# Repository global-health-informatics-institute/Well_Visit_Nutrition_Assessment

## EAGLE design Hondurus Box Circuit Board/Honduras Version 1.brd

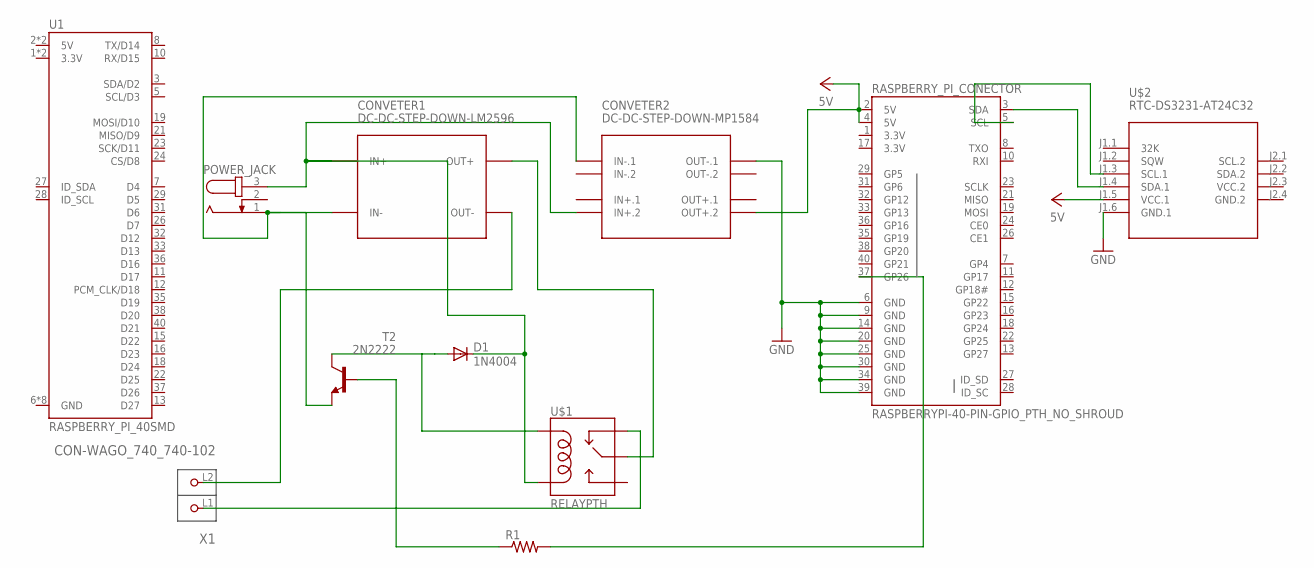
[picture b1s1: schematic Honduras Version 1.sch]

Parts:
CONVETER1: DC-DC-STEP-DOWN-LM2596
CONVETER2: DC-DC-STEP-DOWN-MP1584
D1: 1N4004; DO41-10
POWER_JACK: JACK-PLUG0; SPC4077
R1: R-US_0207/10; 0207/10
RASPBERRY_PI_CONECTOR: RASPBERRYPI-40-PIN-GPIO_PTH_NO_SHROUD; 2X20
T2: 2N2222; TO92-EBC-OVAL
U1: RASPBERRY_PI_40SMD; RASPBERRY_PI_SHIELD_HOLES
U$1: RELAYPTH; SRD-05VDC-SL-C
U$2: RTC-DS3231-AT24C32
X1: CON-WAGO_740_740-102; CON-WAGO_740_P-740-102

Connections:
3.3V: RASPBERRY_PI_CONECTOR.1 (3.3V), RASPBERRY_PI_CONECTOR.17 (3.3V)
GND: CONVETER2.OUT-.1, RASPBERRY_PI_CONECTOR.6 (GND), RASPBERRY_PI_CONECTOR.9 (GND), RASPBERRY_PI_CONECTOR.14 (GND), RASPBERRY_PI_CONECTOR.20 (GND), RASPBERRY_PI_CONECTOR.25 (GND), RASPBERRY_PI_CONECTOR.30 (GND), RASPBERRY_PI_CONECTOR.34 (GND), RASPBERRY_PI_CONECTOR.39 (GND), U$2.J1.6 (GND.1)
GND.2: U$2.J2.4 (GND.2)
unnamed: CONVETER1.IN+, CONVETER2.IN+.2, D1.C, POWER_JACK.3, U$1.COIL0
unnamed: RASPBERRY_PI_CONECTOR.3 (SDA), U$2.J1.4 (SDA.1)
unnamed: RASPBERRY_PI_CONECTOR.5 (SCL), U$2.J1.3 (SCL.1)
unnamed: CONVETER1.OUT-, X1.L2 (P2)
unnamed: CONVETER1.IN-, CONVETER2.IN-.1, POWER_JACK.1, T2.E
unnamed: R1.2, RASPBERRY_PI_CONECTOR.37 (GP26)
unnamed: D1.A, T2.C, U$1.COIL1
unnamed: R1.1, T2.B
unnamed: U$1.SWCLOSED (SWCLOSE), X1.L1 (P1)
unnamed: CONVETER1.OUT+, U$1.SWCOMMON
VCC: CONVETER2.OUT+.2, RASPBERRY_PI_CONECTOR.2 (5V), RASPBERRY_PI_CONECTOR.4 (5V), U$2.J1.5 (VCC.1)
VCC.2: U$2.J2.3 (VCC.2)

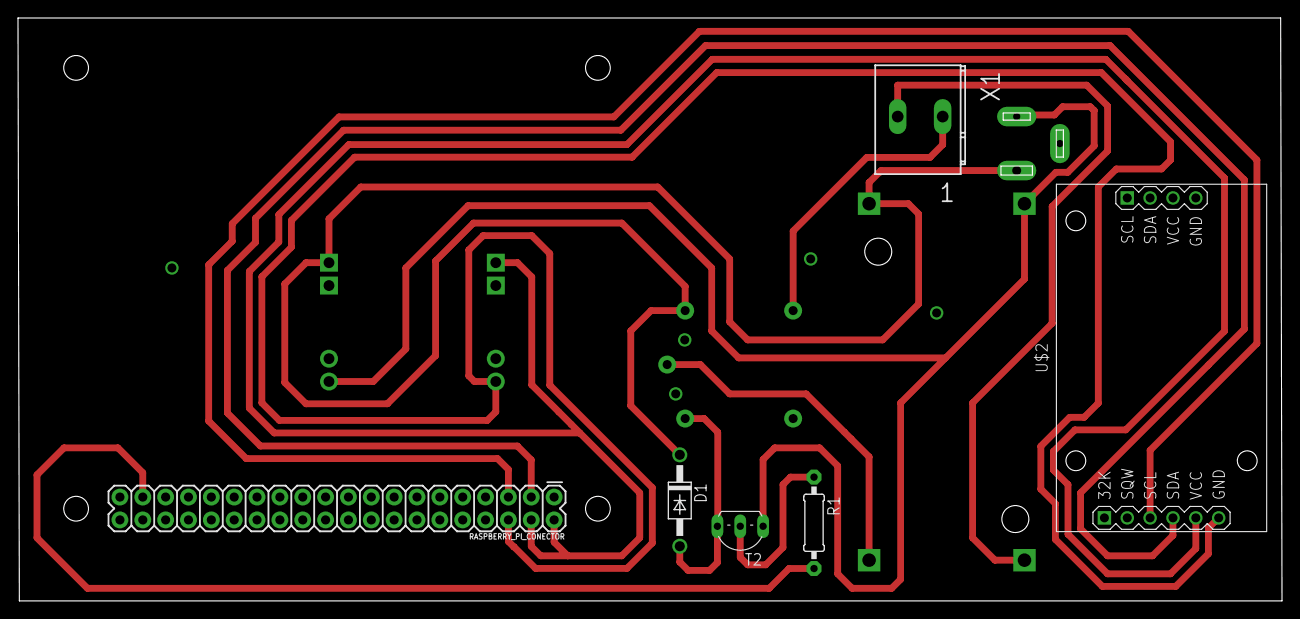
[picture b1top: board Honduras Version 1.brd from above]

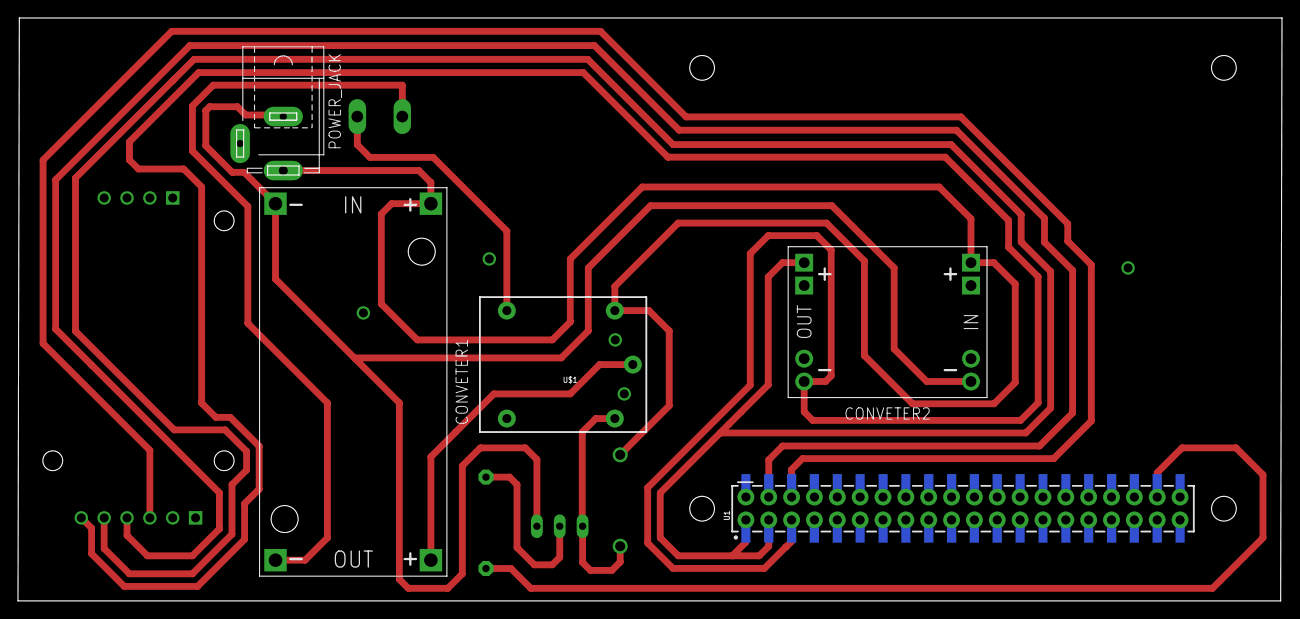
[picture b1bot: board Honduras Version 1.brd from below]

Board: 2 copper layers, 140.5 x 64.8 mm, 11 parts (5 on the bottom side), 13 nets.

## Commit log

2019-09-19 Initital Commit
2019-09-19 Added and edited the gitignore file
2019-10-08 honduras
2019-11-05 second commit
2019-11-14 Update keyboard size and the format of the student_ID
2019-11-29 circuit board for the unit
2020-01-17 Updated the Search Function
2020-01-20 software reads today's date from the RaspberryPi
2020-01-21 update search functionality
2020-01-23 Added Dashboard window
2020-01-24 made a few changes
2020-01-29 added Delete Functionality
2020-01-30 limit height and weight to one dp
2020-01-30 Add files via upload
    Committing the ARM executable version so that Kevin can try to pull it
2020-01-31 updated search function
2020-01-31 This is the Executable file
2020-03-29 updated age functionality

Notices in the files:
parts and their libraries:
SparkFun-Connectors: Licensing: Creative Commons ShareAlike 4.0 International - https://creativecommons.org/licenses/by-sa/4.0
GHIdiy-modules: Released under the Creative Commons Attribution 4.0 International License: http://creativecommons.org/licenses/by/4.0
